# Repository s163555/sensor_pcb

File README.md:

# Sensor\_AFE\_PCB

* [PCB source](https://github.com/adafruit/Adafruit-MAX31865-PCB)
* [Wiki](https://learn.adafruit.com/adafruit-max31865-rtd-pt100-amplifier)

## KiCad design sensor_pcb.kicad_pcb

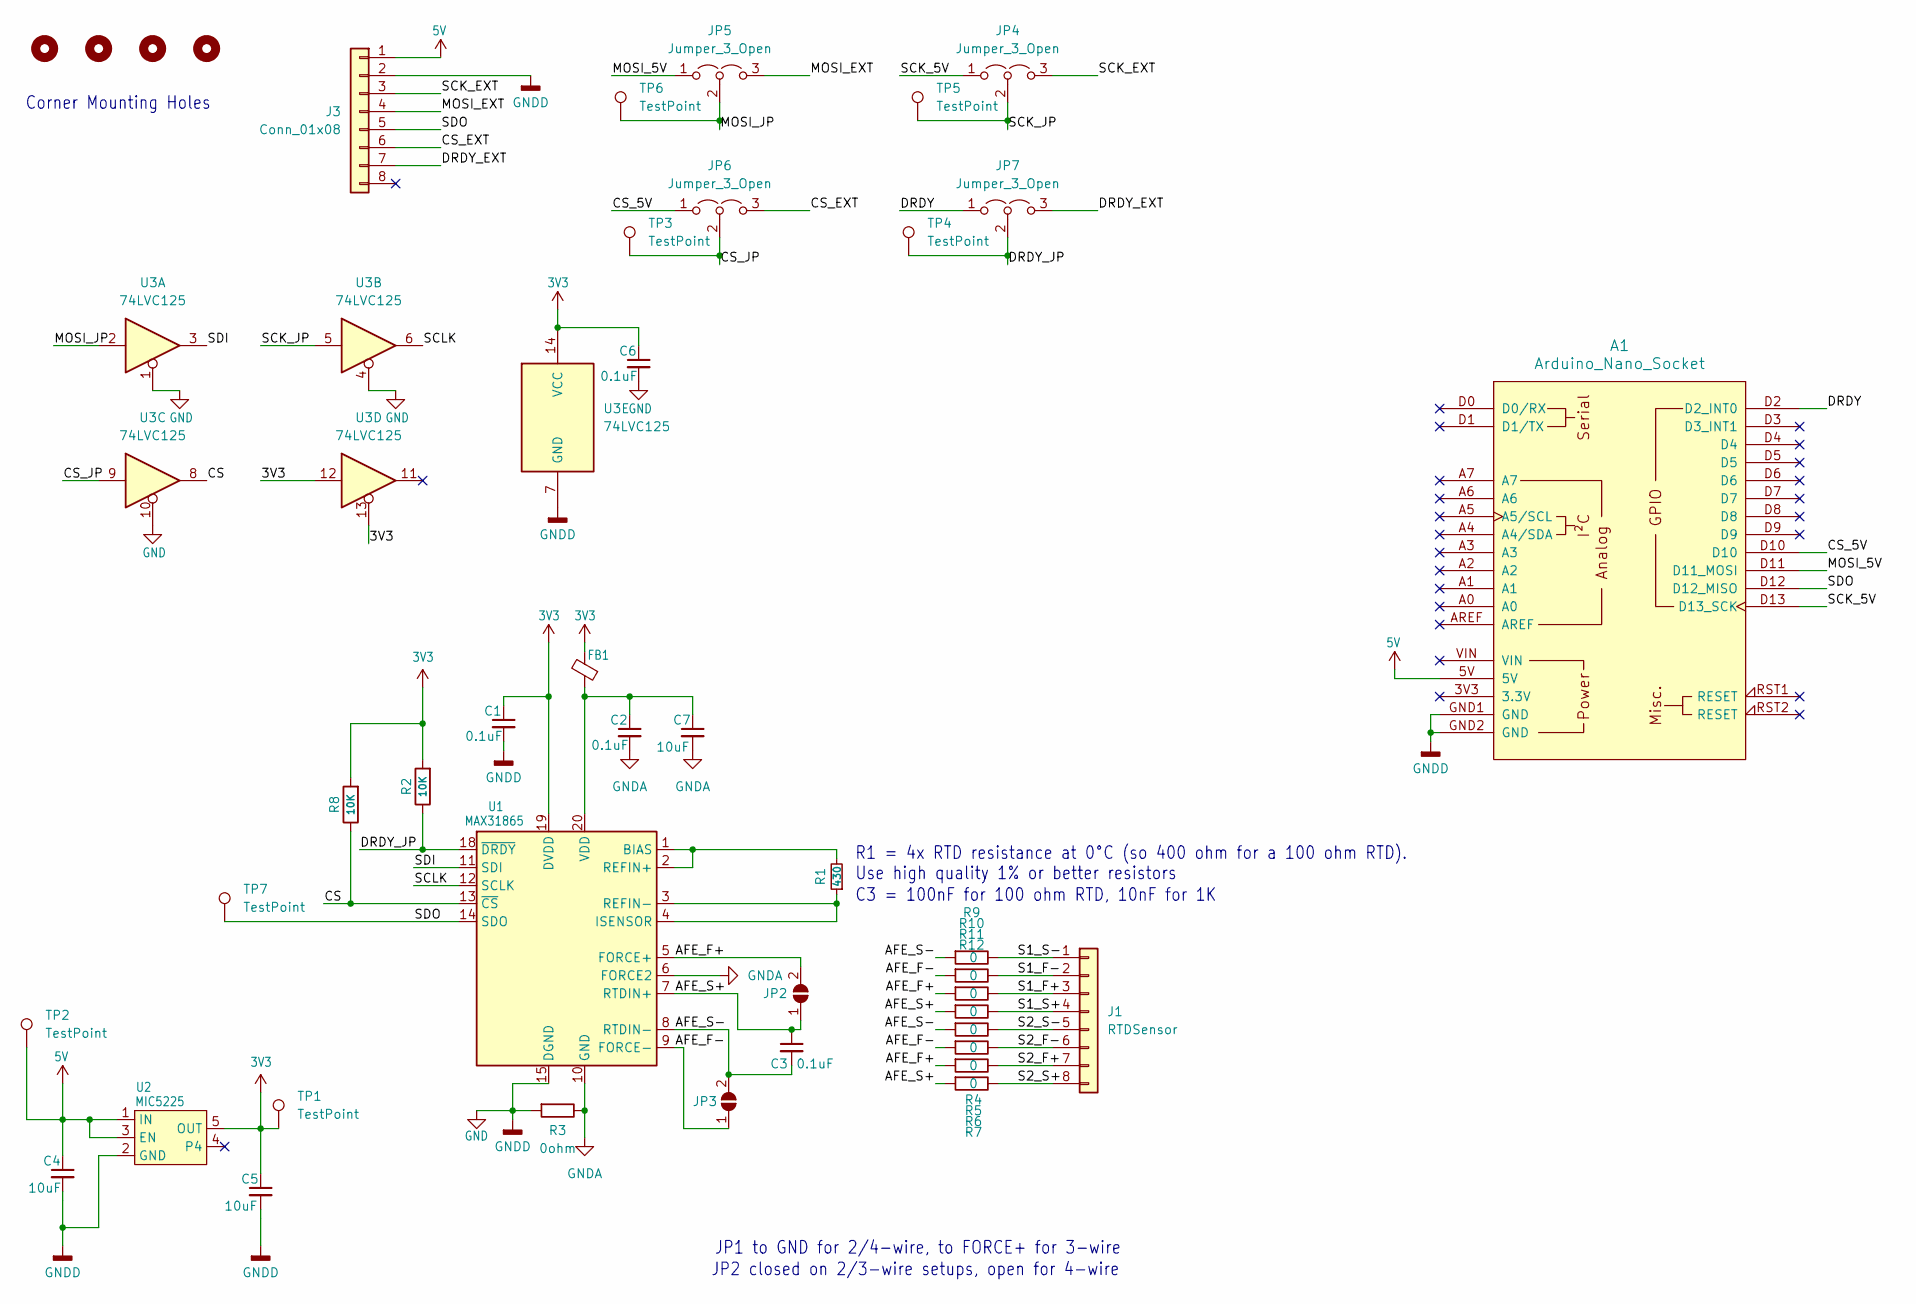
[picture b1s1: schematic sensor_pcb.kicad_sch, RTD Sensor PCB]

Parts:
A1: Arduino_Nano_Socket
C1, C2, C3, C6: 0.1uF; C_0805_2012Metric; MPN /
C4, C5, C7: 10uF; C_0805_2012Metric; MPN /
FB1: FERRITE-0805NO; LI0805G201R-10; MPN LI0805G201R-10
J1: RTDSensor; RTD_Sensor_BondPad_interdigitated
J3: Conn_01x08; Molex_KK-254_AE-6410-08A_1x08_P2.54mm_Vertical
JP2, JP3: SOLDERJUMPER; SolderJumper-2_P1.3mm_Open_RoundedPad1.0x1.5mm
JP4, JP5, JP6, JP7: Jumper_3_Open; PinHeader_1x03_P2.54mm_Vertical
R1: 430; R_0805_2012Metric; Tolerance Plus-Minus 0.1%; MPN /
R2, R8: 10K; R_0805_2012Metric; MPN /
R3: 0ohm; R_0805_2012Metric
R4, R5, R6, R7, R9, R10, R11, R12: 0; R_0805_2012Metric
TP1, TP2, TP3, TP4, TP5, TP6, TP7: TestPoint; TestPoint_Pad_D1.0mm
U1: MAX31865; MAX31865ATP+; MPN MAX31865ATP+
U2: MIC5225; MPN MIC5225-3.3YM5-TR
U3: 74LVC125
U$1, U$2, U$18, U$19: MOUNTINGHOLE2.5; MountingHole_2.2mm_M2_ISO7380

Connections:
3V3: C1.1, C5.1, C6.1, FB1.2, R2.2, R8.2, TP1.1, U1.19 (DVDD), U2.5 (OUT), U3.12, U3.13, U3.14 (VCC)
5V: A1.5V, C4.1, J3.1, TP2.1, U2.1 (IN), U2.3 (EN)
/AFE_F+: JP2.2 (B), R6.1, R11.1, U1.5 (FORCE+)
/AFE_F-: JP3.1 (A), R5.1, R10.1, U1.9 (FORCE-)
/AFE_S+: C3.1, JP2.1 (A), R7.1, R12.1, U1.7 (RTDIN+)
/AFE_S-: C3.2, JP3.2 (B), R4.1, R9.1, U1.8 (RTDIN-)
/CS: R8.1, U1.13 (~CS), U3.8
/CS_5V: A1.D10, JP6.1 (A)
/CS_EXT: J3.6, JP6.3 (B)
/CS_JP: JP6.2 (C), TP3.1, U3.9
/DRDY: A1.D2 (D2_INT0), JP7.1 (A)
/DRDY_EXT: J3.7, JP7.3 (B)
/DRDY_JP: JP7.2 (C), R2.1, TP4.1, U1.18 (~DRDY)
/MOSI_5V: A1.D11 (D11_MOSI), JP5.1 (A)
/MOSI_EXT: J3.4, JP5.3 (B)
/MOSI_JP: JP5.2 (C), TP6.1, U3.2
/S1_F+: J1.3, R11.2
/S1_F-: J1.2, R10.2
/S1_S+: J1.4, R12.2
/S1_S-: J1.1, R9.2
/S2_F+: J1.7, R6.2
/S2_F-: J1.6, R5.2
/S2_S+: J1.8, R7.2
/S2_S-: J1.5, R4.2
/SCK_5V: A1.D13 (D13_SCK), JP4.1 (A)
/SCK_EXT: J3.3, JP4.3 (B)
/SCK_JP: JP4.2 (C), TP5.1, U3.5
/SCLK: U1.12 (SCLK), U3.6
/SDI: U1.11 (SDI), U3.3
/SDO: A1.D12 (D12_MISO), J3.5, TP7.1, U1.14 (SDO)
GND: A1.GND1 (GND), A1.GND2 (GND), C1.2, C4.2, C5.2, C6.2, J3.2, R3.1, U1.15 (DGND), U2.2 (GND), U3.1, U3.4, U3.7 (GND), U3.10
GNDA: C2.2, C7.2, R3.2, U1.6 (FORCE2), U1.10 (GND), U1.16 (GND), U1.21 (GND)
unnamed: R1.2, U1.1 (BIAS), U1.2 (REFIN+)
unnamed: R1.1, U1.3 (REFIN-), U1.4 (ISENSOR)
unnamed: C2.1, C7.1, FB1.1, U1.20 (VDD)

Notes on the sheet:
JP1 to GND for 2/4-wire, to FORCE+ for 3-wire
R1 = 4x RTD resistance at 0°C (so 400 ohm for a 100 ohm RTD). Use high quality 1% or better resistors
Corner Mounting Holes
C3 = 100nF for 100 ohm RTD, 10nF for 1K
JP2 closed on 2/3-wire setups, open for 4-wire

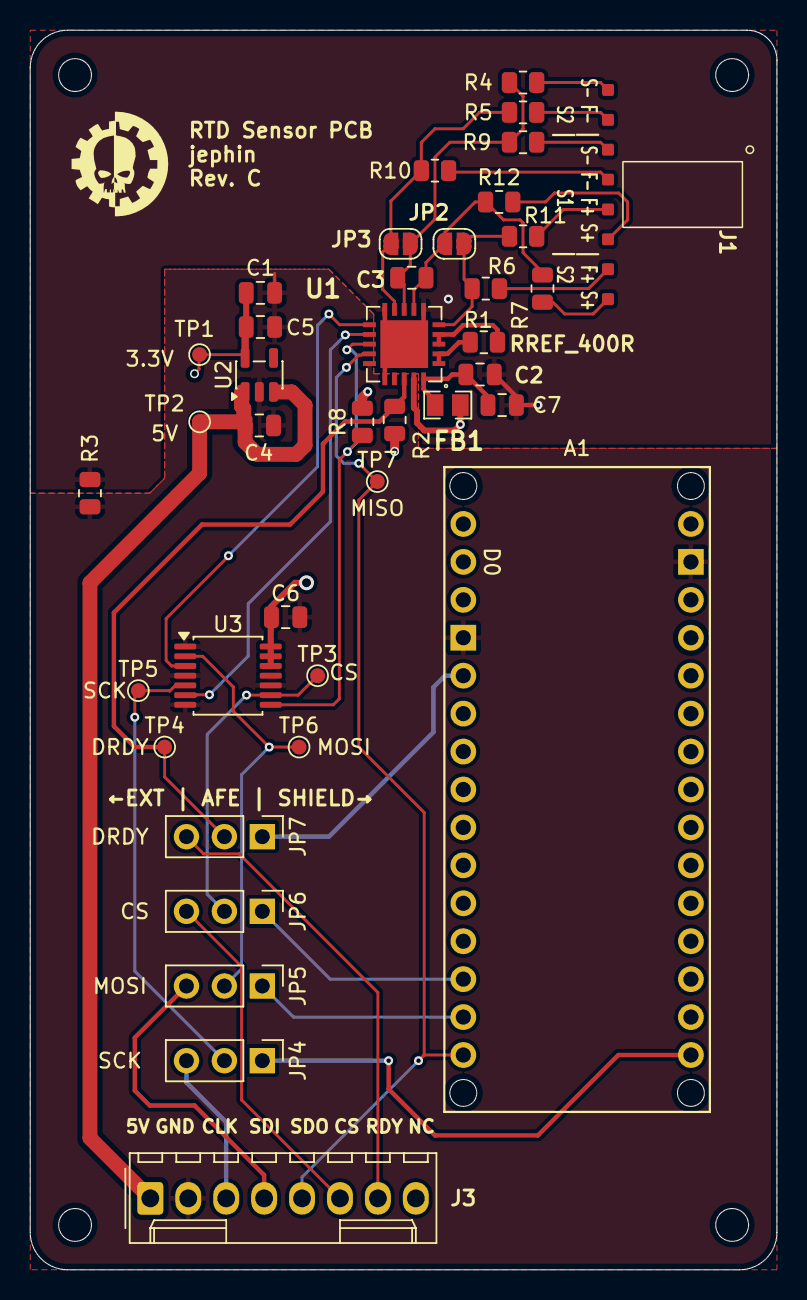
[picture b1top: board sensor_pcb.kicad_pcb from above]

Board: 2 copper layers, 50.0 x 83.0 mm, 43 parts (0 on the bottom side), 35 nets.

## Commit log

2024-03-05 .gitignore update
2024-03-05 blank KiCad project
2024-03-05 Eagle import
2024-03-06 added drawing sheet
2024-03-12 updated all capacitors
2024-03-12 updated all resistors
2024-03-12 updated all vdd
2024-03-12 updated all gnd
2024-03-13 updated all diodes
2024-03-13 updated ferrite bead
2024-03-13 updated solder jumpers
2024-03-13 updated header
2024-03-13 created TODO list in README.md
2024-03-15 updated max31865
2024-03-15 updated screw terminal
2024-03-15 updated vin libraries
2024-03-15 places eagleimport symbol in own library
2024-03-15 changed to own library
2024-03-26 changed all capacitor foorprints in schematic
2024-03-26 changed all capacitor footprints on pcb layout
2024-03-26 changed all resistor footprints in schematic
2024-03-26 changed all diode footprints in schematic
2024-03-26 changed all diode footprints on pcb layout
2024-03-26 changed all connectors footprints in schematic
2024-03-26 changed all connector footprints on pcb layout
2024-03-26 changed connector pin 1x08 footprints in schematic
2024-03-26 changed connector pin 1x08 footprints on pcb layout
2024-03-26 changed mounting hole footprint in schematic and pcb layout
2024-03-26 changed solder footprint in schematic and pcb layout
2024-03-26 changed fiducial footprint in schematic and pcb layout
2024-03-27 changed sot-23-5 footprint in schematic and pcb layout
2024-03-27 changed 3 way solde jumper footprint in schematic and pcb layout
2024-03-27 added ferrite bead symbol and footprint in external library
2024-03-28 fixed routing + added BOM info
2024-03-28 removed imported library
2024-03-28 added missing 3D models
2024-03-28 unnecessary library removed
2024-04-01 improved routing
2024-04-01 silkscreen update
2024-04-03 changed copper finish + solder mask and silkscreen color update
2024-04-04 KiBot DRC check workflow
2024-04-05 dielectric color update
2024-05-17 updated solder jumper
2024-05-17 fixed connection mistake
2024-05-17 schematic update
2024-05-21 implemented Eurocircuits design remarks
2024-06-10 BOM presets update
2025-10-08 Added Nano shield to schematic
2025-10-10 Updated AFE with Arduino shield
2025-10-13 Updated layout
2025-10-13 Added stp for ferrite 0805
2025-10-13 Silkscreen on footprint
2025-10-13 Added fab outputs
2025-10-13 Updated layout constraints
2025-10-13 README updated
2025-10-13 Layout update
2025-10-13 Updated sensor footprint
2025-10-14 updated CI/CD
2025-10-14 updated CI/CD?
2025-10-14 updated CICD??
2025-10-14 updated CICD???
2025-10-14 updated CICD????
2025-10-14 cicd trigger test
2025-10-14 expanded CI/CD to fabrication outputs
2025-10-16 planed supply rails
2025-10-17 Cleaned up footprint library
2025-10-17 commented out pdf outputs
2025-10-17 fixed output names
2025-10-17 trigger cicd
2025-10-17 collected external syms and footprints
2025-10-17 ci external cleanup
2025-10-17 ci on every push
2025-10-17 ci proper fabrication output
2025-10-17 fabrication outputs layout pdf
2025-10-17 fabrication outputs layout pdf 2
2025-10-17 CI releases
2025-10-17 release test
2025-10-17 CI trigger
2025-10-17 gerbers included in outputs
2025-10-17 windåse garbage collection
2025-10-17 CI clean artifact
2025-10-17 CI removed duplicate gerbers
2025-10-17 changed project file names
2025-10-17 release ready
2025-10-17 Single release structure
2025-10-17 removed fabrication outputs from revision control
2025-10-17 Added fabrication folder to gitignore
2025-10-17 fabrication outputs from kibot rather than repo
2025-10-17 added debug to action
2025-10-17 added more debug info
2025-10-17 just work
2025-10-20 Added missing SPN info to parts
2025-10-20 Added fab notes
2025-10-30 RTD sensor wire bonding landing pattern interdigitated
2025-10-30 Updated GND/GNDA planes
2025-10-31 Revision C of layout
2025-11-21 Added MCU firmware for rtd sensor
2025-11-21 extra decimal on temperature readout
2025-12-12 Added fault information to firmware. Added PCB holder 3D model for wire-bonding
2025-12-16 added base plate for mounting to tpt100 chuck
2025-12-17 fixed pcb holder for wire bonder
2025-12-17 reinforced pcb standoffs to sidewall
2025-12-17 added window to base of pcb holder
2026-03-02 added measurement data
2026-03-05 characterization of rtd added
2026-03-10 added plots, resistance vs temperature plot
2026-05-19 technical report
2026-05-19 renamed
